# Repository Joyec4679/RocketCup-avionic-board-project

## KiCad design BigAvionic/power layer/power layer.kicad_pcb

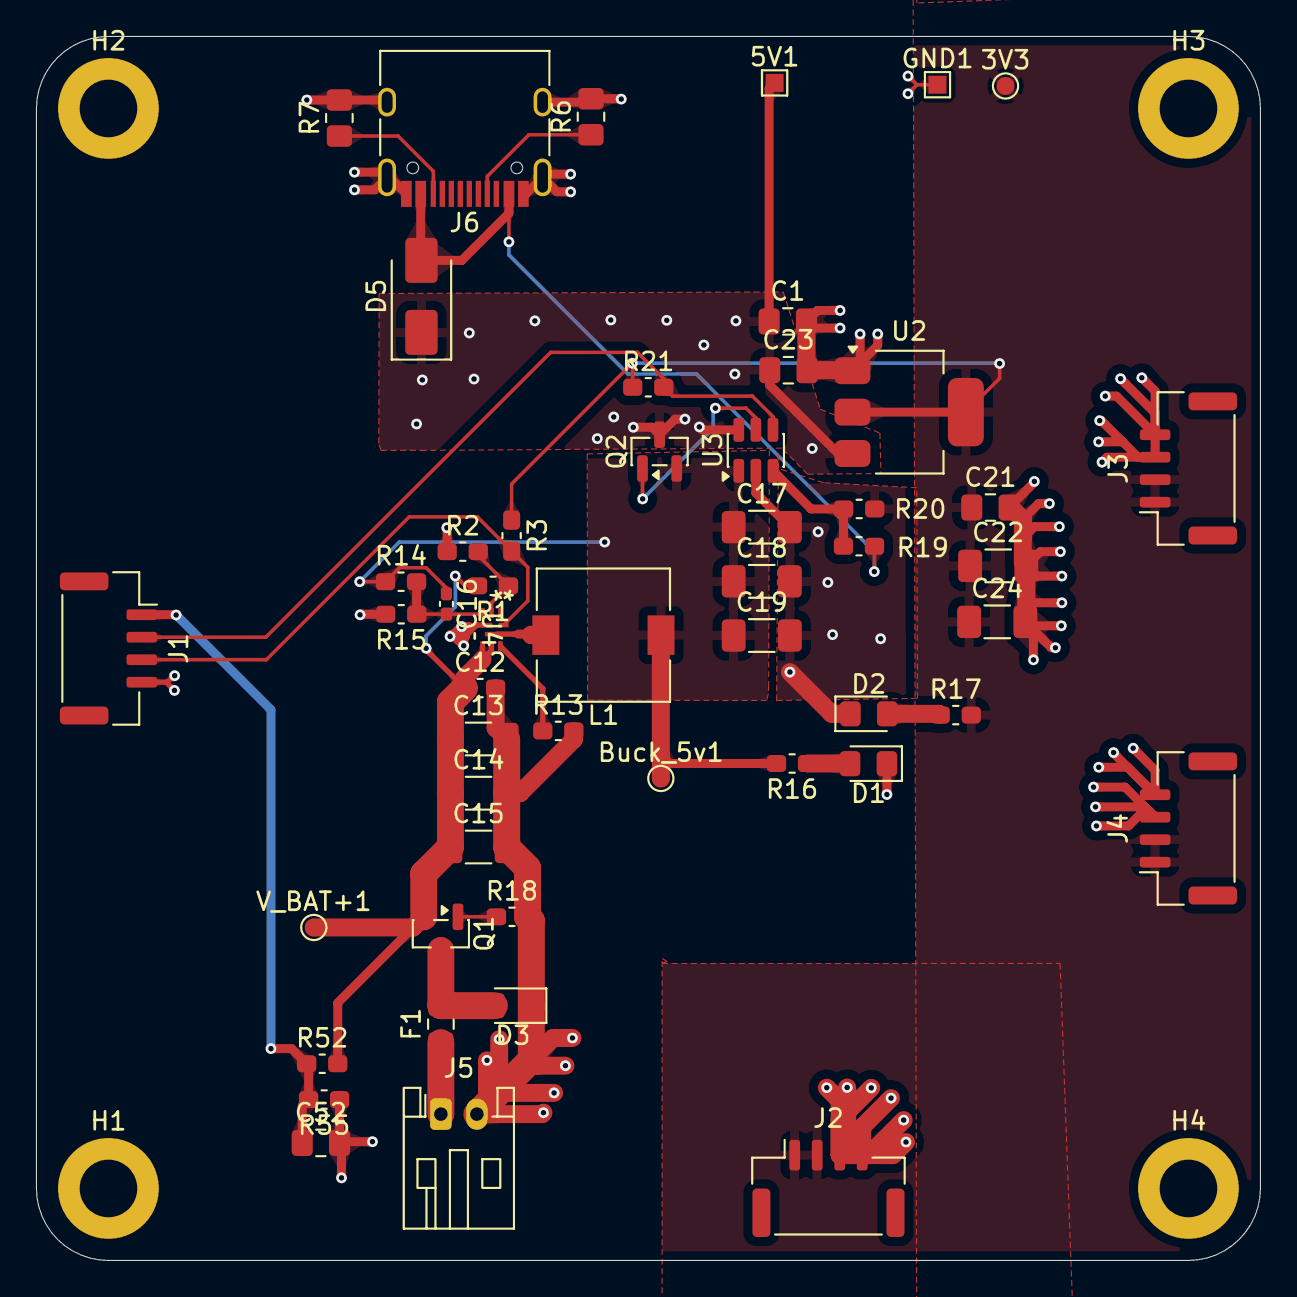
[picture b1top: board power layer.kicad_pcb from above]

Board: 4 copper layers, 68.0 x 68.0 mm, 56 parts (0 on the bottom side), 22 nets.

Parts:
3V3: TestPoint; TestPoint_Pad_D1.0mm
5V1: TestPoint; TestPoint_Pad_1.0x1.0mm
Buck_5v1: TestPoint; TestPoint_Pad_D1.0mm
C1: 10u; C_0805_2012Metric_Pad1.18x1.45mm_HandSolder
C12: 100n; C_0603_1608Metric_Pad1.08x0.95mm_HandSolder
C13, C14, C15: 4.7u; C_1206_3216Metric_Pad1.33x1.80mm_HandSolder
C16: 10p; C_0402_1005Metric_Pad0.74x0.62mm_HandSolder
C17, C18, C19, C22, C24: 47u; C_1206_3216Metric_Pad1.33x1.80mm_HandSolder
C21, C23, C52: 100n; C_0805_2012Metric_Pad1.18x1.45mm_HandSolder
D1: G_5V; LED_0805_2012Metric_Pad1.15x1.40mm_HandSolder
D2: B_3V3; LED_0805_2012Metric_Pad1.15x1.40mm_HandSolder
D3: TVS; LED_0805_2012Metric_Pad1.15x1.40mm_HandSolder
D5: SS24; D_SMA
F1: Fuse; Fuse_0805_2012Metric_Pad1.15x1.40mm_HandSolder
GND1: TestPoint; TestPoint_Pad_1.0x1.0mm
H1, H2, H3, H4: MountingHole; MountingHole_3.2mm_M3_DIN965_Pad
J1, J2, J3, J4: Conn_01x04; JST_GH_SM04B-GHS-TB_1x04-1MP_P1.25mm_Horizontal
J5: Conn_01x02; JST_PH_S2B-PH-K_1x02_P2.00mm_Horizontal
J6: USB_C_Receptacle_USB2.0_16P; USB_C_Receptacle_HRO_TYPE-C-31-M-12
L1: 6.8u; L_7.3x7.3_H3.5
Q1, Q2: TSM3481CX6 RFG; SOT-23
R1: 390k; C_0603_1608Metric_Pad1.08x0.95mm_HandSolder
R2, R3, R18, R19, R21: 100k; C_0603_1608Metric_Pad1.08x0.95mm_HandSolder
R6, R7: 5.1k; R_0805_2012Metric_Pad1.20x1.40mm_HandSolder
R13: 18k; C_0603_1608Metric_Pad1.08x0.95mm_HandSolder
R14: 220k; C_0603_1608Metric_Pad1.08x0.95mm_HandSolder
R15: 30k; C_0603_1608Metric_Pad1.08x0.95mm_HandSolder
R16, R17: 1k; C_0603_1608Metric_Pad1.08x0.95mm_HandSolder
R20: 1M; C_0603_1608Metric_Pad1.08x0.95mm_HandSolder
R52: 10k; C_0603_1608Metric_Pad1.08x0.95mm_HandSolder
R55: 5k; C_0603_1608Metric_Pad1.08x0.95mm_HandSolder
U2: LD1117S33TR_SOT223; SOT-223-3_TabPin2
U3: LTC4412xS6; TSOT-23-6
U4: TPS54538RQFR; VQFN-HR9_RQF_TEX(TPS54538)
V_BAT+1: TestPoint; TestPoint_Pad_D1.0mm

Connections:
5V: 5V1.1, C1.1, C23.1, D5.1 (K), Q2.3 (D), U2.3 (VI), U3.6 (SENSE)
+3.3V: 3V3.1, C21.1, C22.1, C24.1, J2.1, J2.2, J3.1, J3.2, J4.1, J4.2, R3.1, R17.2, R21.1, U2.2 (VO)
+USB_5V: D5.2 (A), J6.A4 (VBUS), J6.A9 (VBUS), J6.B4 (VBUS), J6.B9 (VBUS), R19.2
BUCK_5V: Buck_5v1.1, C16.1, C17.1, C18.1, C19.1, L1.1, Q2.2 (S), R14.1, R16.2, U3.1 (VIN)
Battery_Sensing: C52.1, J1.1, R52.1, R55.2
GND: C1.2, C12.2, C13.2, C14.2, C15.2, C17.2, C18.2, C19.2, C21.2, C22.2, C23.2, C24.2, C52.2, D1.1 (K), D2.1 (K), D3.1 (A1), GND1.1, J1.4, J2.3, J2.4, J3.3, J3.4, J4.3, J4.4, J5.2, J6.A1 (GND), J6.A12 (GND), J6.B1 (GND), J6.B12 (GND), J6.S1 (SHIELD), R2.1, R6.2, R7.2, R13.2, R15.2, R18.2, R20.2, R55.1, U2.1 (GND), U3.2 (GND), U4.4 (GND)
unnamed: D1.2 (A), R16.1
unnamed: D2.2 (A), R17.1
unnamed: D3.2 (A2), F1.2, Q1.3 (D)
unnamed: F1.1, J5.1
unnamed: J6.A5 (CC1), R6.1
unnamed: J6.B5 (CC2), R7.1
unnamed: Q1.1 (G), R18.1
unnamed: Q2.1 (G), U3.5 (GATE)
unnamed: R19.1, R20.1, U3.3 (CTL)
unnamed: R1.1, R2.2, U4.2 (EN)
unnamed: C16.2, R14.2, R15.1, U4.3 (FB)
unnamed: R13.1, U4.7 (MODE)
unnamed: L1.2, U4.8 (SW)
PG_BUCK: J1.3, R3.2, U4.9 (SS/PG)
SUP_STAT: J1.2, R21.2, U3.4 (STAT)
V_BAT+: C12.1, C13.1, C14.1, C15.1, Q1.2 (S), R1.2, R52.2, U4.5 (VIN), U4.6 (VIN), V_BAT+1.1
